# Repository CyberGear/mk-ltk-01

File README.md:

# Bleeding Charcoal (mk-ltk-01)

[First Idea](./images/mk-ltk-01.png)

## Details
* **Keeb**: Black steel dust painted plate, sandwich case, stained plywood
* **Kaycaps**: [Aliexpress ones](https://www.aliexpress.com/item/1005001285224963.html?spm=a2g0s.9042311.0.0.27424c4dBEbhVW) also custom painted for accent caps
* **Switches**: Gateron brown, Lubed with Krytox 205g0, and filmed.
* **Stabs**: [Aliexpress ones](https://www.aliexpress.com/item/10000249766414.html?spm=a2g0s.9042311.0.0.27424c4dtrbYE2) lubed and cliped a lot :D

## Initial Requirements
* As low prifile as possible
* Reasonable price around 100€ (failed! 170€)
* NOT flat profile keycaps
* Tactile
* Left side num pad
* Stardart layout (keycaps wise)
* Make most space for mouse withour loosing functionality (on the right)

## Tools
* http://www.keyboard-layout-editor.com
* http://builder.swillkb.com/
* https://kbfirmware.com/
* https://noroadsleft.github.io/kbf_qmk_converter/

## Decisions made
* Sandwich case (stained plywood and painted black steel)
*  
  Unfortunatelly to high for low profile switches
* Diodes 1N4148
* Gateron Brown
* Plate mounted stabs from Aliexpress
* Krytox GPL 205 G0
* Switch Films
* Teensy 2.0++

## Progress

Metal parts :) 

Put foam for sound dampening (legacy acrylic frame)

Plywood case V1

Wrist rest :D 

New desk mat

Lubing and filling switches

Fit test "naked"

Fit test full case

Screwless top

USB type-C cutout

Switch matrix ([mirrored](./images/switch-matrix-mirror.png))

Wiring

Usb type-c Integration

More foam

Total foam

Suprisingly Simple Adjustable Legs

Custom Spray Painted Keycaps

Stained plywood finish

Wire

RESULT

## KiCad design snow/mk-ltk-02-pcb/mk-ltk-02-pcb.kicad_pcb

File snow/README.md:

# Kit contents

1. *Plate* - dust painted aluminum
2. *PCB* - also white
3. *Bottom plate* - dust painted steel
4. *USB socket* - fits in one of those cuts in PCB
5. *Socket soldering template* - to help to solder it straight
6. *4 small rubber feet*

# Features

1. Left ten keys layout (southpaw layout) 
2. Intelligently mirrored num pan layout 
3. PCB features:
    1. Supports MX switches 
    2. Supports kailh hot-swappable sockets 
    3. Supports thru-hole diods 
    4. Supports surface mount diodes 

# Required additional parts

1. Teensy ® ++ 2.0
2. Full set of keycaps (recommend flat layout, because of 'Home' and 'End' possitions)
4. Full set of stabilizers 
    1. Plate mounted works out of the box
    2. PCB mounted requires addition filing of switch plate :/ 
5. 108 x MX switches
6. 108 x 1N4148 diods
7. 20 x M2 screws
8. 10 x 9mm M2 spacers (if You remove mini USB from teensy)
9. USB Type-C cable

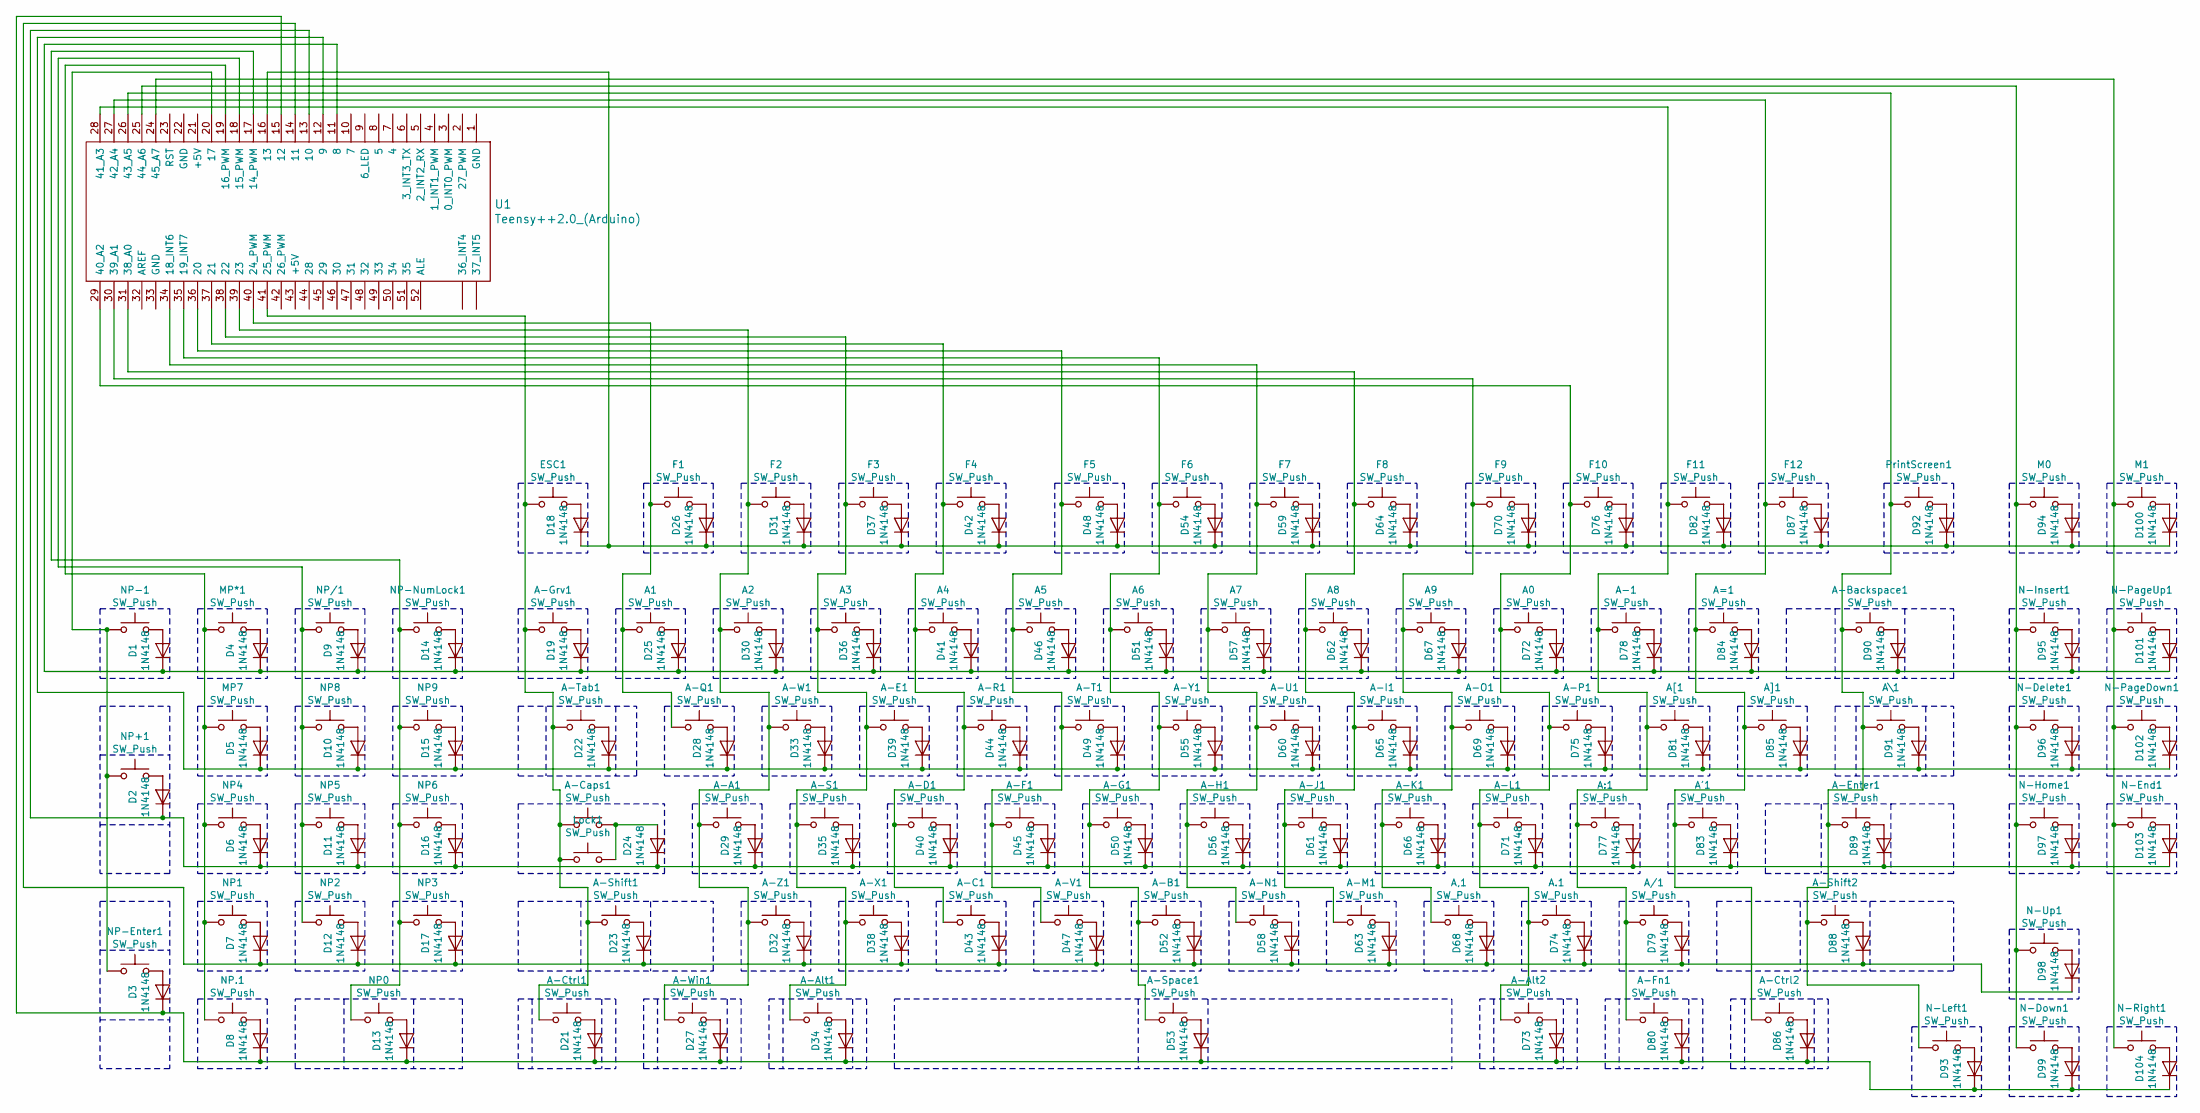
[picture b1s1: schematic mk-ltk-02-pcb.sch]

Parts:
A0, A1, A2, A3, A4, A5, A6, A7, A8, A9, A.1: SW_Push; Kailh_socket_MX_optional
A'1: SW_Push; Kailh_socket_MX_optional
A,1: SW_Push; Kailh_socket_MX_optional
A-1: SW_Push; Kailh_socket_MX_optional
A-A1: SW_Push; Kailh_socket_MX_optional
A-Alt1, A-Alt2: SW_Push; Kailh_socket_MX_optional
A-B1: SW_Push; Kailh_socket_MX_optional
A-Backspace1: SW_Push; Kailh_socket_MX_optional
A-C1: SW_Push; Kailh_socket_MX_optional
A-Caps1: SW_Push; Kailh_socket_MX_optional
A-Ctrl1, A-Ctrl2: SW_Push; Kailh_socket_MX_optional
A-D1: SW_Push; Kailh_socket_MX_optional
A-E1: SW_Push; Kailh_socket_MX_optional
A-Enter1: SW_Push; Kailh_socket_MX_optional
A-F1: SW_Push; Kailh_socket_MX_optional
A-Fn1: SW_Push; Kailh_socket_MX_optional
A-G1: SW_Push; Kailh_socket_MX_optional
A-Grv1: SW_Push; Kailh_socket_MX_optional
A-H1: SW_Push; Kailh_socket_MX_optional
A-I1: SW_Push; Kailh_socket_MX_optional
A-J1: SW_Push; Kailh_socket_MX_optional
A-K1: SW_Push; Kailh_socket_MX_optional
A-L1: SW_Push; Kailh_socket_MX_optional
A-M1: SW_Push; Kailh_socket_MX_optional
A-N1: SW_Push; Kailh_socket_MX_optional
A-O1: SW_Push; Kailh_socket_MX_optional
A-P1: SW_Push; Kailh_socket_MX_optional
A-Q1: SW_Push; Kailh_socket_MX_optional
A-R1: SW_Push; Kailh_socket_MX_optional
A-S1: SW_Push; Kailh_socket_MX_optional
A-Shift1, A-Shift2: SW_Push; Kailh_socket_MX_optional
A-Space1: SW_Push; Kailh_socket_MX_optional
A-T1: SW_Push; Kailh_socket_MX_optional
A-Tab1: SW_Push; Kailh_socket_MX_optional
A-U1: SW_Push; Kailh_socket_MX_optional
A-V1: SW_Push; Kailh_socket_MX_optional
A-W1: SW_Push; Kailh_socket_MX_optional
A-Win1: SW_Push; Kailh_socket_MX_optional
A-X1: SW_Push; Kailh_socket_MX_optional
A-Y1: SW_Push; Kailh_socket_MX_optional
A-Z1: SW_Push; Kailh_socket_MX_optional
A/1: SW_Push; Kailh_socket_MX_optional
A:1: SW_Push; Kailh_socket_MX_optional
A=1: SW_Push; Kailh_socket_MX_optional
A[1: SW_Push; Kailh_socket_MX_optional
A\1: SW_Push; Kailh_socket_MX_optional
A]1: SW_Push; Kailh_socket_MX_optional
D1, D2, D3, D4, D5, D6, D7, D8, D9, D10, D11, D12, D13, D14, D15, D16, D17, D18, D19, D21, D22, D23, D24, D25, D26, D27, D28, D29, D30, D31, D32, D33, D34, D35, D36, D37, D38, D39, D40, D41, D42, D43, D44, D45, D46, D47, D48, D49, D50, D51, D52, D53, D54, D55, D56, D57, D58, D59, D60, D61, D62, D63, D64, D65, D66, D67, D68, D69, D70, D71, D72, D73, D74, D75, D76, D77, D78, D79, D80, D81, D82, D83, D84, D85, D86, D87, D88, D89, D90, D91, D92, D93, D94, D95, D96, D97, D98, D99, D100, D101, D102, D103, D104: 1N4148; Diode-smd-tht
ESC1: SW_Push; Kailh_socket_MX_optional
F1, F2, F3, F4, F5, F6, F7, F8, F9, F10, F11, F12: SW_Push; Kailh_socket_MX_optional
Lock1: SW_Push; Kailh_socket_MX_optional
M0, M1: SW_Push; Kailh_socket_MX_optional
MP7: SW_Push; Kailh_socket_MX_optional
MP*1: SW_Push; Kailh_socket_MX_optional
N-Delete1: SW_Push; Kailh_socket_MX_optional
N-Down1: SW_Push; Kailh_socket_MX_optional
N-End1: SW_Push; Kailh_socket_MX_optional
N-Home1: SW_Push; Kailh_socket_MX_optional
N-Insert1: SW_Push; Kailh_socket_MX_optional
N-Left1: SW_Push; Kailh_socket_MX_optional
N-PageDown1: SW_Push; Kailh_socket_MX_optional
N-PageUp1: SW_Push; Kailh_socket_MX_optional
N-Right1: SW_Push; Kailh_socket_MX_optional
N-Up1: SW_Push; Kailh_socket_MX_optional
NP0, NP1, NP2, NP3, NP4, NP5, NP6, NP8, NP9, NP.1: SW_Push; Kailh_socket_MX_optional
NP+1: SW_Push; Kailh_socket_MX_optional
NP-1: SW_Push; Kailh_socket_MX_optional
NP-Enter1: SW_Push; Kailh_socket_MX_optional
NP-NumLock1: SW_Push; Kailh_socket_MX_optional
NP/1: SW_Push; Kailh_socket_MX_optional
PrintScreen1: SW_Push; Kailh_socket_MX_optional
U1: Teensy++2.0_(Arduino); Teensy2.0++

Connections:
unnamed: A0.2, D72.2 (A)
unnamed: A1.2, D25.2 (A)
unnamed: A2.2, D30.2 (A)
unnamed: A3.2, D36.2 (A)
unnamed: A4.2, D41.2 (A)
unnamed: A5.2, D46.2 (A)
unnamed: A6.2, D51.2 (A)
unnamed: A7.2, D57.2 (A)
unnamed: A8.2, D62.2 (A)
unnamed: A9.2, D67.2 (A)
unnamed: A'1.1, A-Ctrl2.1, A=1.1, A]1.1, F12.1, U1.27 (42_A4)
unnamed: A'1.2, D83.2 (A)
unnamed: A9.1, A,1.1, A-K1.1, A-O1.1, F9.1, U1.30 (39_A1)
unnamed: A,1.2, D68.2 (A)
unnamed: A-1.1, A-Fn1.1, A/1.1, A:1.1, A[1.1, F11.1, U1.28 (41_A3)
unnamed: A-1.2, D78.2 (A)
unnamed: A2.1, A-A1.1, A-W1.1, A-Win1.1, A-Z1.1, F2.1, U1.39 (23)
unnamed: A-A1.2, D29.2 (A)
unnamed: A3.1, A-Alt1.1, A-E1.1, A-S1.1, A-X1.1, F3.1, U1.38 (22)
unnamed: A-Alt1.2, D34.2 (A)
unnamed: A0.1, A-Alt2.1, A-L1.1, A-P1.1, A.1.1, F10.1, U1.29 (40_A2)
unnamed: A-Alt2.2, D73.2 (A)
unnamed: A6.1, A-B1.1, A-G1.1, A-Space1.1, A-Y1.1, F6.1, U1.35 (19_INT7)
unnamed: A-B1.2, D52.2 (A)
unnamed: A-Backspace1.1, A-Enter1.1, A-Shift2.1, A\1.1, N-Left1.1, PrintScreen1.1, U1.26 (43_A5)
unnamed: A-Backspace1.2, D90.2 (A)
unnamed: A4.1, A-C1.1, A-D1.1, A-R1.1, F4.1, U1.37 (21)
unnamed: A-C1.2, D43.2 (A)
unnamed: A-Caps1.1, A-Ctrl1.1, A-Grv1.1, A-Shift1.1, A-Tab1.1, ESC1.1, Lock1.1, U1.41 (25_PWM)
unnamed: A-Caps1.2, D24.2 (A), Lock1.2
unnamed: A-Ctrl1.2, D21.2 (A)
unnamed: A-Ctrl2.2, D86.2 (A)
unnamed: A-D1.2, D40.2 (A)
unnamed: A-E1.2, D39.2 (A)
unnamed: A-Enter1.2, D89.2 (A)
unnamed: A5.1, A-F1.1, A-T1.1, A-V1.1, F5.1, U1.36 (20)
unnamed: A-F1.2, D45.2 (A)
unnamed: A-Fn1.2, D80.2 (A)
unnamed: A-G1.2, D50.2 (A)
unnamed: A-Grv1.2, D19.2 (A)
unnamed: A7.1, A-H1.1, A-N1.1, A-U1.1, F7.1, U1.34 (18_INT6)
unnamed: A-H1.2, D56.2 (A)
unnamed: A8.1, A-I1.1, A-J1.1, A-M1.1, F8.1, U1.31 (38_A0)
unnamed: A-I1.2, D65.2 (A)
unnamed: A-J1.2, D61.2 (A)
unnamed: A-K1.2, D66.2 (A)
unnamed: A-L1.2, D71.2 (A)
unnamed: A-M1.2, D63.2 (A)
unnamed: A-N1.2, D58.2 (A)
unnamed: A-O1.2, D69.2 (A)
unnamed: A-P1.2, D75.2 (A)
unnamed: A1.1, A-Q1.1, F1.1, U1.40 (24_PWM)
unnamed: A-Q1.2, D28.2 (A)
unnamed: A-R1.2, D44.2 (A)
unnamed: A-S1.2, D35.2 (A)
unnamed: A-Shift1.2, D23.2 (A)
unnamed: A-Shift2.2, D88.2 (A)
unnamed: A-Space1.2, D53.2 (A)
unnamed: A-T1.2, D49.2 (A)
unnamed: A-Tab1.2, D22.2 (A)
unnamed: A-U1.2, D60.2 (A)
unnamed: A-V1.2, D47.2 (A)
unnamed: A-W1.2, D33.2 (A)
unnamed: A-Win1.2, D27.2 (A)
unnamed: A-X1.2, D38.2 (A)
unnamed: A-Y1.2, D55.2 (A)
unnamed: A-Z1.2, D32.2 (A)
unnamed: A.1.2, D74.2 (A)
unnamed: A/1.2, D79.2 (A)
unnamed: A:1.2, D77.2 (A)
unnamed: A=1.2, D84.2 (A)
unnamed: A[1.2, D81.2 (A)
unnamed: A\1.2, D91.2 (A)
unnamed: A]1.2, D85.2 (A)
unnamed: D1.1 (K), D4.1 (K), D9.1 (K), D14.1 (K), D19.1 (K), D25.1 (K), D30.1 (K), D36.1 (K), D41.1 (K), D46.1 (K), D51.1 (K), D57.1 (K), D62.1 (K), D67.1 (K), D72.1 (K), D78.1 (K), D84.1 (K), D90.1 (K), D95.1 (K), D101.1 (K), U1.11 (8)
unnamed: D1.2 (A), NP-1.2
unnamed: D2.2 (A), NP+1.2
unnamed: D3.2 (A), NP-Enter1.2
unnamed: D4.2 (A), MP*1.2
unnamed: D5.2 (A), MP7.2
unnamed: D6.2 (A), NP4.2
unnamed: D7.2 (A), NP1.2
unnamed: D8.2 (A), NP.1.2
unnamed: D9.2 (A), NP/1.2
unnamed: D5.1 (K), D10.1 (K), D15.1 (K), D22.1 (K), D28.1 (K), D33.1 (K), D39.1 (K), D44.1 (K), D49.1 (K), D55.1 (K), D60.1 (K), D65.1 (K), D69.1 (K), D75.1 (K), D81.1 (K), D85.1 (K), D91.1 (K), D96.1 (K), D102.1 (K), U1.12 (9)
unnamed: D10.2 (A), NP8.2
unnamed: D11.2 (A), NP5.2
unnamed: D7.1 (K), D12.1 (K), D17.1 (K), D23.1 (K), D32.1 (K), D38.1 (K), D43.1 (K), D47.1 (K), D52.1 (K), D58.1 (K), D63.1 (K), D68.1 (K), D74.1 (K), D79.1 (K), D88.1 (K), D98.1 (K), U1.14 (11)
unnamed: D12.2 (A), NP2.2
unnamed: D13.2 (A), NP0.2
unnamed: D14.2 (A), NP-NumLock1.2
unnamed: D15.2 (A), NP9.2
unnamed: D16.2 (A), NP6.2
unnamed: D17.2 (A), NP3.2
unnamed: D18.2 (A), ESC1.2
unnamed: D26.2 (A), F1.2
unnamed: D31.2 (A), F2.2
unnamed: D37.2 (A), F3.2
unnamed: D42.2 (A), F4.2
unnamed: D48.2 (A), F5.2
unnamed: D54.2 (A), F6.2
unnamed: D59.2 (A), F7.2
unnamed: D64.2 (A), F8.2
unnamed: D70.2 (A), F9.2
unnamed: D76.2 (A), F10.2
unnamed: D82.2 (A), F11.2
unnamed: D87.2 (A), F12.2
unnamed: D92.2 (A), PrintScreen1.2
unnamed: D93.2 (A), N-Left1.2
unnamed: D94.2 (A), M0.2
unnamed: D95.2 (A), N-Insert1.2
unnamed: D96.2 (A), N-Delete1.2
unnamed: D97.2 (A), N-Home1.2
unnamed: D98.2 (A), N-Up1.2
unnamed: D99.2 (A), N-Down1.2
unnamed: D18.1 (K), D26.1 (K), D31.1 (K), D37.1 (K), D42.1 (K), D48.1 (K), D54.1 (K), D59.1 (K), D64.1 (K), D70.1 (K), D76.1 (K), D82.1 (K), D87.1 (K), D92.1 (K), D94.1 (K), D100.1 (K), U1.16 (13)
unnamed: D100.2 (A), M1.2
unnamed: D101.2 (A), N-PageUp1.2
unnamed: D102.2 (A), N-PageDown1.2
unnamed: D2.1 (K), D6.1 (K), D11.1 (K), D16.1 (K), D24.1 (K), D29.1 (K), D35.1 (K), D40.1 (K), D45.1 (K), D50.1 (K), D56.1 (K), D61.1 (K), D66.1 (K), D71.1 (K), D77.1 (K), D83.1 (K), D89.1 (K), D97.1 (K), D103.1 (K), U1.13 (10)
unnamed: D103.2 (A), N-End1.2
unnamed: D3.1 (K), D8.1 (K), D13.1 (K), D21.1 (K), D27.1 (K), D34.1 (K), D53.1 (K), D73.1 (K), D80.1 (K), D86.1 (K), D93.1 (K), D99.1 (K), D104.1 (K), U1.15 (12)
unnamed: D104.2 (A), N-Right1.2
unnamed: M0.1, N-Delete1.1, N-Down1.1, N-Home1.1, N-Insert1.1, N-Up1.1, U1.25 (44_A6)
unnamed: M1.1, N-End1.1, N-PageDown1.1, N-PageUp1.1, N-Right1.1, U1.24 (45_A7)
unnamed: MP7.1, MP*1.1, NP1.1, NP4.1, NP.1.1, U1.19 (16_PWM)
unnamed: NP+1.1, NP-1.1, NP-Enter1.1, U1.20 (17)
unnamed: NP0.1, NP3.1, NP6.1, NP9.1, NP-NumLock1.1, U1.17 (14_PWM)
unnamed: NP2.1, NP5.1, NP8.1, NP/1.1, U1.18 (15_PWM)

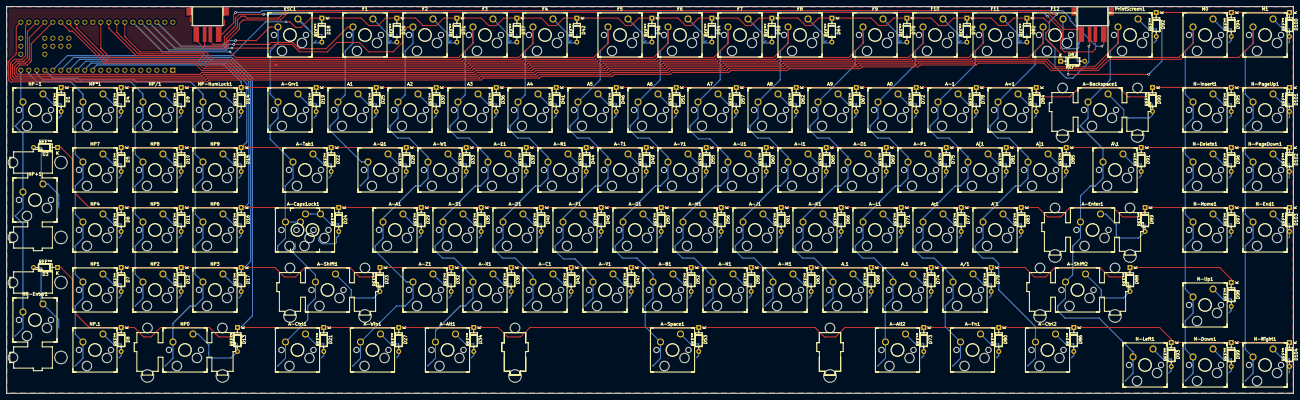
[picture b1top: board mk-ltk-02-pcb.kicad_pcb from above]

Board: 2 copper layers, 408.5 x 122.8 mm, 208 parts (1 on the bottom side), 129 nets.

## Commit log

2020-08-24 initialize a repository
2020-08-25 add visualisation
2020-08-25 update visualisation
2020-08-28 update preview again
2020-08-29 define requirements
2020-08-29 update switch options
2020-09-11 add sandwich case files
2020-09-11 add model zip
2020-09-11 reupload case files
2020-10-25 update preview image
2020-10-26 update top and closed layers
2020-10-31 add v1 top 3d model
2021-01-13 rearanging with latest project 1
2021-01-13 rearanging with latest project 2
2021-01-13 rearanging with latest project 3
2021-01-13 rearanging with latest project 4
2021-01-13 rearanging with latest project 5
2021-01-14 paint job
2021-01-21 qmk firmware v01
2021-01-21 giving a name
2021-01-22 more progress
2021-01-22 final progress
2021-01-22 add details
2021-01-22 type
2021-04-24 add pcb project v1
2021-04-27 add usb cutouts and ground plane
2021-09-21 add snow firmware
2021-09-21 fix firmware, readme
